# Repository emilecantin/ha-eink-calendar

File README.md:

# E-Ink Calendar Display

A battery-powered IoT calendar display that shows your Home Assistant calendar events on a large 12.48" tri-color e-paper screen.

## Features

- **Large e-paper display** — Waveshare 12.48" tri-color (black/white/red)
- **Battery optimized** — Deep sleep between updates, ETag caching to skip unnecessary refreshes
- **Native HA integration** — Custom component with Python renderer, no external server needed
- **Device discovery** — ESP32 auto-discovers HA via mDNS, appears as a discovered device
- **Weather integration** — Shows daily forecast from any HA weather entity
- **Waste collection** — Icon-only display for waste/recycling calendars
- **Multi-language** — French and English, configurable per device
- **Multi-device** — Each ESP32 gets its own config entry with independent settings

## Hardware Requirements

- [Waveshare E-Paper ESP32 Driver Board](https://www.waveshare.com/wiki/E-Paper_ESP32_Driver_Board) (or compatible ESP32)
- [Waveshare 12.48" e-Paper Module (B)](https://www.waveshare.com/12.48inch-e-paper-module-b.htm) — tri-color version
- USB cable for programming
- Optional: battery for portable operation

## Installation

### Home Assistant Integration

Install via HACS using the badge above, or manually:

1. Copy `custom_components/eink_calendar/` to your HA `config/custom_components/` directory
2. Restart Home Assistant
3. Go to **Settings** > **Devices & Services** > **Add Integration**
4. Search for "E-Ink Calendar" and follow the setup wizard

### Configuration

Each device is configured through the HA UI with these options:

| Option | Description |
|--------|-------------|
| **Calendars** | Which calendar entities to display with full event details |
| **Waste Calendars** | Calendar entities shown as icons only (e.g., garbage/recycling) |
| **Language** | Display language — French or English |
| **Layout** | Landscape (recommended) or Portrait |
| **Show Legend** | Show calendar icon legend at the bottom |
| **Weather Entity** | Optional weather entity for daily forecast |
| **Refresh Interval** | How often the ESP32 checks for updates (minutes) |
| **Custom Fonts** | Optional paths to custom TTF fonts (Regular, Medium, Bold) |

All options can be changed later in **Settings > Devices & Services > E-Ink Calendar > Configure**.

### Entities Created

Each device creates:

| Entity | Description |
|--------|-------------|
| `camera.{name}_preview` | Full-color PNG preview of the calendar |
| `image.{name}_black_layer_top` | Top half of the black bitmap layer |
| `image.{name}_black_layer_bottom` | Bottom half of the black bitmap layer |
| `image.{name}_red_layer_top` | Top half of the red bitmap layer |
| `image.{name}_red_layer_bottom` | Bottom half of the red bitmap layer |
| `sensor.{name}_last_update` | Timestamp of the last render |
| `sensor.{name}_last_checkin` | Timestamp of the last ESP32 check-in |

## ESP32 Firmware

The firmware is in `Arduino/epcal/` and uses PlatformIO.

### Building and Uploading

```bash
cd Arduino/epcal
pio run -t upload
```

### First-Time Setup

1. Power on the ESP32 — the display shows QR codes for WiFi and config URL
2. Connect your phone to the **EinkCal-Setup** WiFi network
3. Open `http://192.168.4.1` or scan the config QR code
4. Enter your WiFi credentials and click Save

The ESP32 will automatically:
- Connect to WiFi
- Discover Home Assistant via mDNS
- Announce itself — a "Discovered" card appears in **Settings > Integrations**
- After you configure it in HA, the calendar displays automatically

To re-enter setup mode, hold the BOOT button for 2 seconds during startup.

### How Updates Work

1. ESP32 wakes from deep sleep
2. Sends a check request to HA with its current ETag
3. HA fetches fresh calendar/weather data and renders the bitmap
4. If the render changed → ESP32 downloads new bitmaps and refreshes the display
5. If unchanged → HA returns 304, ESP32 skips the download (saves battery)
6. ESP32 goes back to deep sleep for the configured refresh interval

The refresh interval is propagated from HA to the ESP32 via HTTP headers, so changing it in the HA config takes effect on the next check-in.

## Display Layout

### Landscape (Recommended) — 1304×984

```
+---------------------------+--------------------------------------------------+
|                           |  LUN  |  MAR  |  MER  |  JEU  |  VEN  |  SAM  |
|  Today                    |  Weather icon + hi/lo temps                      |
|  Day name + date          |  Events for each day                             |
|  Weather + events         |                                                  |
|                           |--------------------------------------------------|
|  Calendar legend          |  Upcoming — events beyond the 6-day view         |
+---------------------------+--------------------------------------------------+
```

## Architecture

```
Home Assistant
  ├── Calendar entities (data source)
  ├── Weather entity (optional)
  └── E-Ink Calendar integration
        ├── Coordinator (fetches data on ESP32 check-in)
        ├── Renderer (generates bitmap from events + weather)
        ├── Announce API (device discovery, no auth)
        └── Bitmap API (serves layers, MAC-based auth)

ESP32
  ├── mDNS discovery → finds HA
  ├── Announce → registers with HA
  ├── Check → triggers render, gets ETag
  ├── Fetch → downloads changed bitmaps
  └── Display → renders on e-paper, deep sleeps
```

## API Endpoints

| Endpoint | Auth | Description |
|----------|------|-------------|
| `POST /api/eink_calendar/announce` | None | Device discovery and status check |
| `GET /api/eink_calendar/bitmap/{entry_id}/{layer}` | X-MAC header | Bitmap serving |
| `GET /api/eink_calendar/bitmap/{entry_id}/check` | X-MAC header | ETag check (triggers re-render) |

## Troubleshooting

### Display shows "M1 Busy" and hangs
Ensure `DEV_ModuleInit()` is called before `EPD_12in48B_Init()` in the firmware.

### ESP32 can't find Home Assistant
- Ensure mDNS is working on your network (HA must be discoverable via `_home-assistant._tcp`)
- As a fallback, enter the HA URL manually in the WiFi setup portal
- Both devices must be on the same network/VLAN

### No events showing
- Ensure at least one calendar is selected in the integration options
- Check that the calendar entities have events in the displayed date range
- Check HA logs for "Calendar entities not ready" errors after restart (normal — HA retries automatically)

### Calendar shows wrong language
Change the **Language** setting in the device options (**Settings > Devices & Services > E-Ink Calendar > Configure**).

### Weather not showing
- Some weather integrations don't include today in their daily forecast — the integration falls back to current conditions automatically
- Verify the weather entity has data in **Developer Tools > States**

## Battery Life

With a 2000mAh battery and 15-minute refresh interval:
- Most check-ins result in 304 Not Modified (~5s active time)
- Full bitmap refresh only when calendar data changes (~15s active time)
- Expected battery life: weeks to months depending on how often events change

## Development

### Running Tests

```bash
cd custom_components/eink_calendar/tests
./run_tests.sh
```

64 unit tests covering event processing, filtering, weather utilities, rendering, and visual regression.

You can filter tests with pytest arguments:

```bash
./run_tests.sh -k "weather"        # Only weather tests
./run_tests.sh -k "process_events" # Only event processing tests
```

### Test Environment

```bash
docker-compose up  # Starts HA with the component mounted
```

### Project Structure

```
epcal/
├── Arduino/epcal/                  # ESP32 firmware (PlatformIO)
│   └── src/
│       ├── epcal.ino              # Main sketch (mDNS + announce + display)
│       ├── config.*               # NVS storage for HA URL, endpoints
│       ├── display.*              # E-paper display driver
│       └── http_client.*          # HTTP client (announce + ETag)
├── custom_components/eink_calendar/ # Home Assistant custom component
│   ├── renderer/                   # Python calendar renderer
│   │   ├── i18n.py                # French/English translations
│   │   ├── section_renderers/     # Today, week, upcoming panels
│   │   └── renderer.py           # Main render pipeline
│   ├── tests/                     # Unit and integration tests
│   ├── config_flow.py            # Discovery + manual config flow
│   ├── coordinator.py            # Data coordinator (on-demand refresh)
│   ├── http_views.py             # Announce + bitmap API
│   └── services.py               # trigger_render service
├── docs/                          # Technical documentation
└── docker-compose.yml             # HA test environment
```

## Contributing

Issues and pull requests welcome at https://github.com/emilecantin/ha-eink-calendar

## License

MIT

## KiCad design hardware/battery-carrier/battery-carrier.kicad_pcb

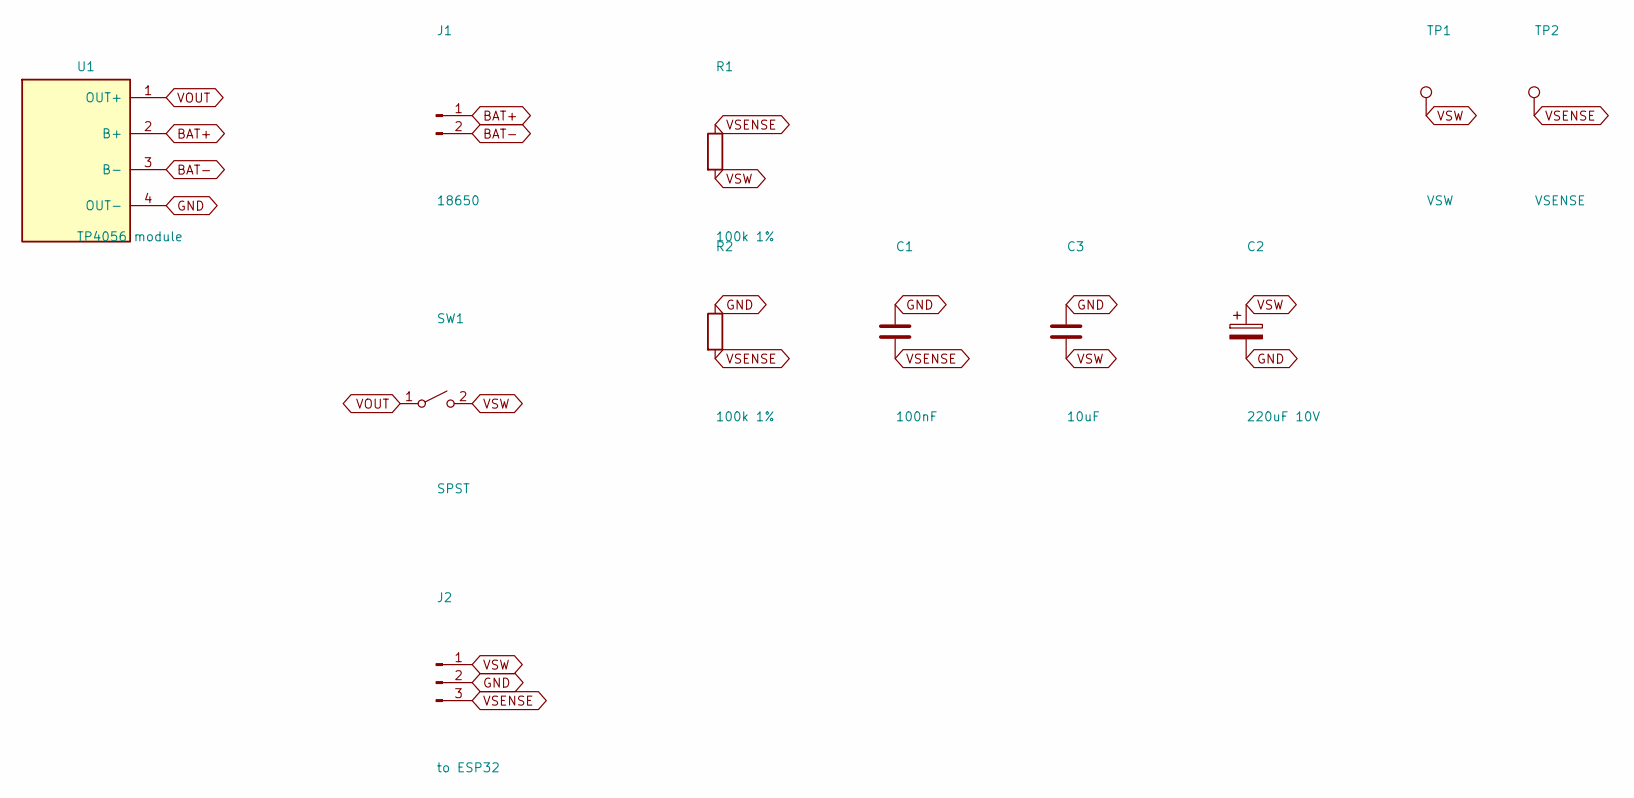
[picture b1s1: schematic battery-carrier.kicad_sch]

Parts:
C1: 100nF; C_0805_2012Metric
C2: 220uF 10V; CP_Elec_6.3x3.9
C3: 10uF; C_0805_2012Metric
J1: 18650; JST_PH_B2B-PH-K_1x02_P2.00mm_Vertical
J2: to ESP32; JST_PH_B3B-PH-K_1x03_P2.00mm_Vertical
R1, R2: 100k 1%; R_0805_2012Metric
SW1: SPST; SW_DIP_SPSTx01_Slide_9.78x4.72mm_W7.62mm_P2.54mm
TP1: VSW; TestPoint_THTPad_1.5x1.5mm_Drill0.7mm
TP2: VSENSE; TestPoint_THTPad_1.5x1.5mm_Drill0.7mm
U1: TP4056 module; TP4056_Module_03962A

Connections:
BAT+: J1.1, U1.2 (B+)
BAT-: J1.2, U1.3 (B-)
GND: C1.1, C2.2, C3.1, J2.2, R2.1, U1.4 (OUT-)
VOUT: SW1.1 (A), U1.1 (OUT+)
VSENSE: C1.2, J2.3, R1.1, R2.2, TP2.1
VSW: C2.1, C3.2, J2.1, R1.2, SW1.2 (B), TP1.1

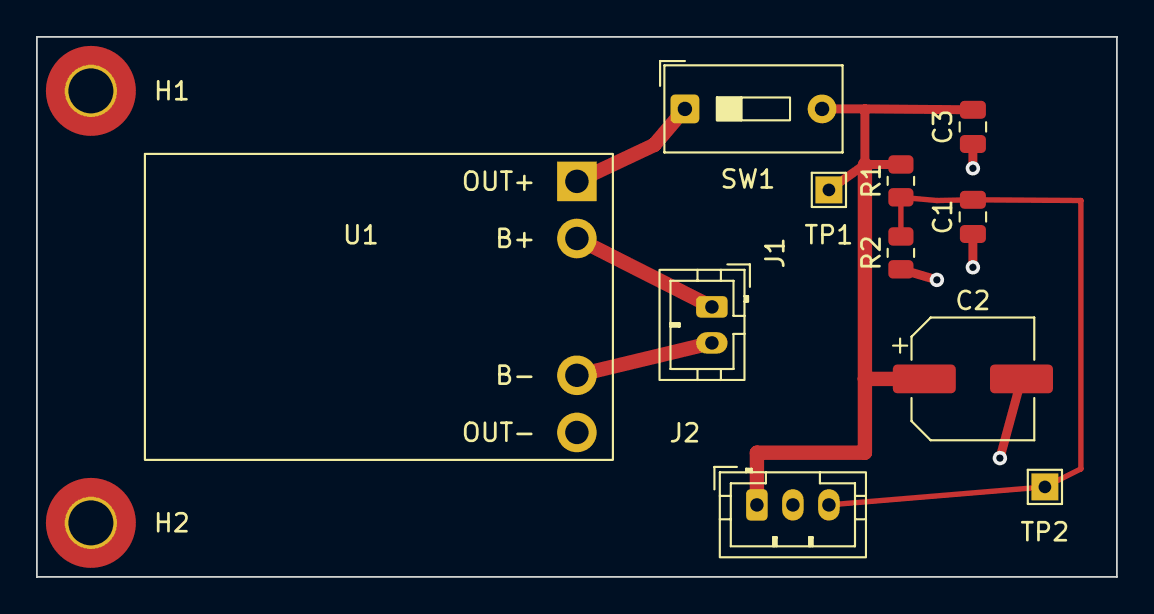
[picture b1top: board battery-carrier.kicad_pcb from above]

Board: 2 copper layers, 60.0 x 30.0 mm, 13 parts (0 on the bottom side), 6 nets.

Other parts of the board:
H1, H2: MountingHole_2.5mm_Pad_TopBottom

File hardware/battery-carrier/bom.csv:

"Reference","Value","Footprint"
"C1","100nF","Capacitor_SMD:C_0805_2012Metric"
"C2","220uF 10V","Capacitor_SMD:CP_Elec_6.3x3.9"
"C3","10uF","Capacitor_SMD:C_0805_2012Metric"
"J1","18650","Connector_JST:JST_PH_B2B-PH-K_1x02_P2.00mm_Vertical"
"J2","to ESP32","Connector_JST:JST_PH_B3B-PH-K_1x03_P2.00mm_Vertical"
"R1,R2","100k 1%","Resistor_SMD:R_0805_2012Metric"
"SW1","SPST","Button_Switch_THT:SW_DIP_SPSTx01_Slide_9.78x4.72mm_W7.62mm_P2.54mm"
"U1","TP4056 module","epcal:TP4056_Module_03962A"

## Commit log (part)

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2026-01-21 Fix double-subtraction of end date for multi-day all-day events
    The end date for all-day events was being converted from exclusive to
    inclusive twice:
    1. Once in index.ts when parsing from Home Assistant
    2. Again in renderer.ts when drawing the event
    This caused multi-day events to show incorrect end markers (both start
    and end triangles on the first day instead of just the start triangle).
2026-01-21 Unify event filtering logic across all calendar sections
    Extract common event filtering logic into getEventsForDay() function that:
    - Filters events for a specific day (events starting OR spanning that day)
    - Returns EventForDay objects with startsOnDay/endsOnDay indicators
    Apply this consistently to all sections:
    - Landscape Today section
    - Landscape 6-day section
2026-01-21 Add collection calendar icons feature
    - Add support for marking calendars as 'collection calendars' in config UI
    - Configure collection types (garbage, recycling, compost) with MDI icons
    - Auto-detect collection events from French event titles
    - Display red collection icons in day headers (Today: 18px, Week: 14px)
    - Icons appear in lower-right corner of day cells
    - Server-side PNG rendering with async icon loading
2026-01-21 Refactor: Extract event rendering helpers (Phase 1)
    - Create server/event-renderer.ts with reusable helper functions
    - Extract drawEventTriangle for all-day event indicators
    - Extract formatMultiDayTime for multi-day arrow formatting
    - Extract drawOverflowIndicator for '+X more events' display
    - Extract sortEventsByPriority for consistent event ordering
    - Update renderer.ts to use new helpers (removes ~50 lines of duplication)
2026-01-21 Phase 2: Extract layout constants into layout-config.ts
    - Create server/layout-config.ts with centralized constants for:
    - Display dimensions (portrait/landscape)
    - Section layouts and margins
    - Typography (all font sizes)
    - Icon sizes
    - Event dimensions
2026-01-21 Phase 3: Create rendering type definitions
    - Create server/rendering-types.ts with comprehensive type definitions
    - Define types for:
    - CalendarEvent, DayForecast, LegendItem, IndicatorData
    - RenderingContext (consolidates 9-10 params into single object)
    - RenderingOptions (optional parameters)
    - SectionBounds, EventRenderStyle, SectionConfig
2026-01-21 Phase 5: Cleanup debug code and re-enable caching
    - Remove collection icon cache clearing on server restart
    - Re-enable icon caching for better performance
    - Remove debug console.log statements from:
    - loadCollectionIcon: Loading, image dimensions logs
    - drawCollectionIcon: Drawing coordinates, success logs
    - getCollectionIconsForDay: Event matching, icon return logs
2026-01-21 Phase 4: Refactor function signatures with context objects
    - Add context-based wrapper functions (V2) for:
    - drawLandscapeTodaySectionV2
    - drawLandscapeWeekSectionV2
    - drawLandscapeUpcomingSectionV2
    - Consolidate 9-10 parameters into single RenderingContext object
    - Update renderCalendarLandscape to use new wrapper functions
2026-01-21 Add ESLint with async/await rules to catch promise bugs
2026-01-21 Fix ESLint errors and adjust config for Express patterns
    - Fixed return await in haFetch()
    - Fixed unused variables (prefix with _)
    - Removed unused Image import from renderer.ts
    - Adjusted ESLint config to be less strict:
    - Downgraded no-misused-promises for Express handlers
    - Downgraded unsafe-* rules to warnings (too strict for HA API)
2026-01-21 Add Jest unit testing setup with comprehensive tests
    - Installed Jest, ts-jest, and testing dependencies
    - Created Jest configuration for TypeScript
    - Added test scripts: test, test:watch, test:coverage
    - Created event-renderer tests:
    - Triangle drawing (left/right direction)
    - Multi-day time formatting
2026-01-21 Add comprehensive test suites for date utils, collection icons, and bitmap conversion
    - date-utils.test.ts: 21 tests for date comparison, formatting, and multi-day event handling
    - collection-icons.test.ts: 14 tests for collection icon matching and async loading patterns
    - bitmap-conversion.test.ts: 12 tests for e-paper bitmap encoding and chunking
    - All 71 tests passing across 5 test suites
    - Tests validate critical functionality and prevent regression of async/await bugs
2026-01-21 Add unit tests for renderer extractChunk function
    - 9 tests covering e-paper display bitmap chunking
    - Tests vertical split (top/bottom 492 rows each)
    - Validates correct chunk sizes (80,196 bytes per chunk)
    - Tests row boundary calculations and memory views
    - All 80 tests passing across 6 test suites
    - Renderer coverage increased from 0% to 4.54%
2026-01-21 Enhance renderer tests with comprehensive coverage
    - Added 6 new test cases for extractChunk function
    - Test all-black and all-white bitmaps
    - Test memory/performance characteristics (zero-copy views)
    - Test ESP32 integration workflow
    - Verify chunk sizes fit ESP32 memory constraints
    - Test horizontal display splitting for proper rendering
2026-01-21 Export renderer helper functions for testing
    - Export 8 helper functions from renderer.ts for unit testing:
    - getIconCenterOffset, getIconBottomOffset (icon positioning)
    - getWeatherIcon (weather condition mapping)
    - formatTime (time formatting)
    - truncateText, wrapText (text layout)
    - rotateImageData90CW (image rotation for portrait mode)
2026-01-22 Refactor server rendering code into modular architecture
    - Extract utilities into focused modules:
    - text-utils.ts: Text formatting (truncate, wrap, capitalize, formatTime)
    - weather-utils.ts: Weather icons and forecast handling
    - icon-utils.ts: Collection icon loading, caching, and positioning
    - event-filters.ts: Event filtering and collection icon matching
    - bitmap-utils.ts: Image rotation, 1-bit conversion, chunk extraction
2026-01-22 Add coverage/ to .gitignore
2026-01-22 Fix ESLint errors in refactored rendering code
    - Remove unused variable imports in section renderers
    - Prefix unused function parameters with underscore
    - Remove unused extractChunk import (kept as re-export only)
    All 154 tests passing. No linting errors in new modules.
2026-01-22 Fix ESLint errors in test files
    - Remove unused beforeEach import in event-renderer.test.ts
    - Add await to return statement in async-patterns.test.ts
    - Prefix unused error variable with underscore in async-patterns.test.ts
    All ESLint errors now fixed. Only warnings remain (mostly in index.ts).
    All 154 tests passing.
2026-01-28 Refactor: Organize TypeScript server build output and utilities
    - Configure TypeScript to output to dist/ folder with source maps
    - Update package.json main entry to dist/index.js
    - Add clean script to rebuild from scratch
    - Move ts-node to devDependencies (only needed for dev)
    - Organize utility scripts into server/scripts/ directory
    - Disable antialiasing in renderer to match Python PIL output
2026-01-28 Add Home Assistant custom component with Python renderer
    - Complete EPCAL integration for Home Assistant
    - Python renderer matching TypeScript output pixel-perfect
    - Support for both portrait and landscape orientations
    - Calendar event rendering with icons, all-day events, multi-day events
    - Weather integration with forecast display
    - Waste collection calendar support
2026-01-28 Refactor: Organize project structure and documentation
    - Create scripts/ directory for developer utilities
    - Move analyze_diffs.py and analyze_diffs_simple.py
    - Move run_tests.py
    - Add README documenting each script
    - Organize test data in tests/fixtures/
    - Move test_scenarios.json
2026-01-28 Add Home Assistant test environment to docker-compose
    - Add homeassistant service for integration development
    - Mount custom_components/epcal and ha-test-config
    - Move legacy server to 'legacy' profile (docker-compose --profile legacy up)
    - Add healthcheck for HA service
    - Configure timezone and host network mode
2026-01-28 Remove obsolete files
    - Remove TODO.md (tasks tracked in issues instead)
    - Remove old screenshot (moved to docs/screenshots)
2026-01-28 Update .gitignore for development artifacts
    - Ignore server/epcal-config.json (local config)
    - Ignore server/__tests__/*.js (test files)
    - Ignore server/icons_svg_cache/ (downloaded icons)
    - Ignore Arduino/epcal/setup_screen_preview.png (generated preview)
